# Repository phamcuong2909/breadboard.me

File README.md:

# breadboard.me
This contains all the sample codes and other resources for my blog at http://www.breadboard.me

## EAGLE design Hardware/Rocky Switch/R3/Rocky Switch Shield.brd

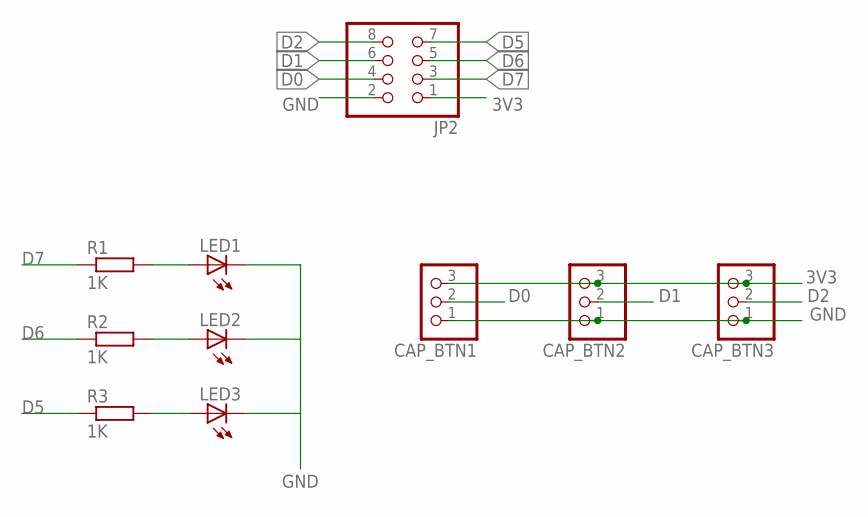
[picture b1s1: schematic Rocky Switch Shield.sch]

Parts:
CAP_BTN1, CAP_BTN2, CAP_BTN3: PINHD-1X3; 1X03
JP2: PINHD-2X4; 2X04
LED1, LED2, LED3: LED3MM
R1, R2, R3: 1K; R0805

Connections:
3V3: CAP_BTN1.3, CAP_BTN2.3, CAP_BTN3.3, JP2.1
D0: CAP_BTN1.2, JP2.4
D1: CAP_BTN2.2, JP2.6
D2: CAP_BTN3.2, JP2.8
D5: JP2.7, R3.1
D6: JP2.5, R2.1
D7: JP2.3, R1.1
GND: CAP_BTN1.1, CAP_BTN2.1, CAP_BTN3.1, JP2.2, LED1.K (C), LED2.K (C), LED3.K (C)
unnamed: LED2.A, R2.2
unnamed: LED3.A, R3.2
unnamed: LED1.A, R1.2

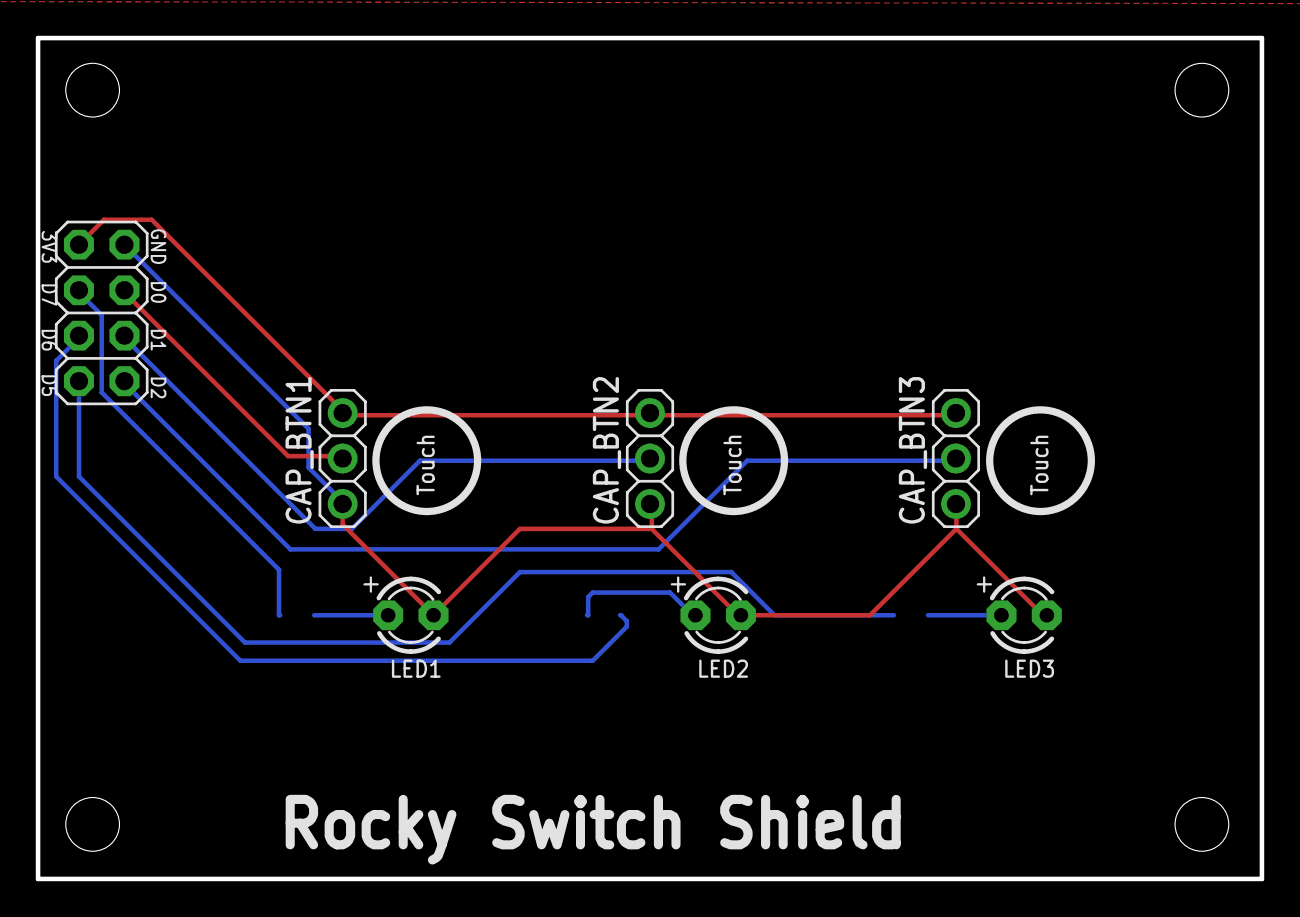
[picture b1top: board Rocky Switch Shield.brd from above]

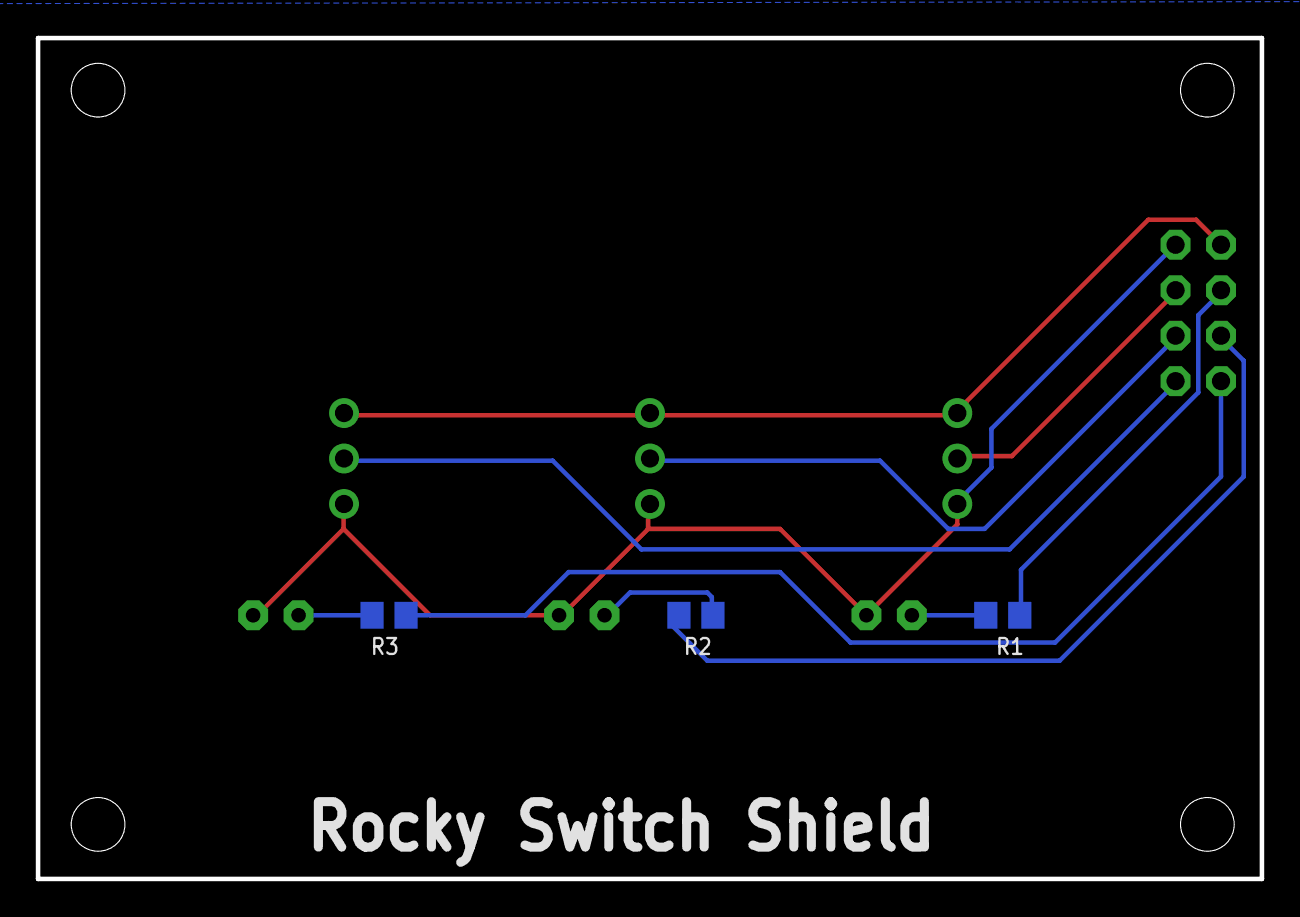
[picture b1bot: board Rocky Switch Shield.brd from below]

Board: 2 copper layers, 68.4 x 47.0 mm, 14 parts (3 on the bottom side), 11 nets.

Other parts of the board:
U$6, U$7, U$8, U$9: KFH-M3

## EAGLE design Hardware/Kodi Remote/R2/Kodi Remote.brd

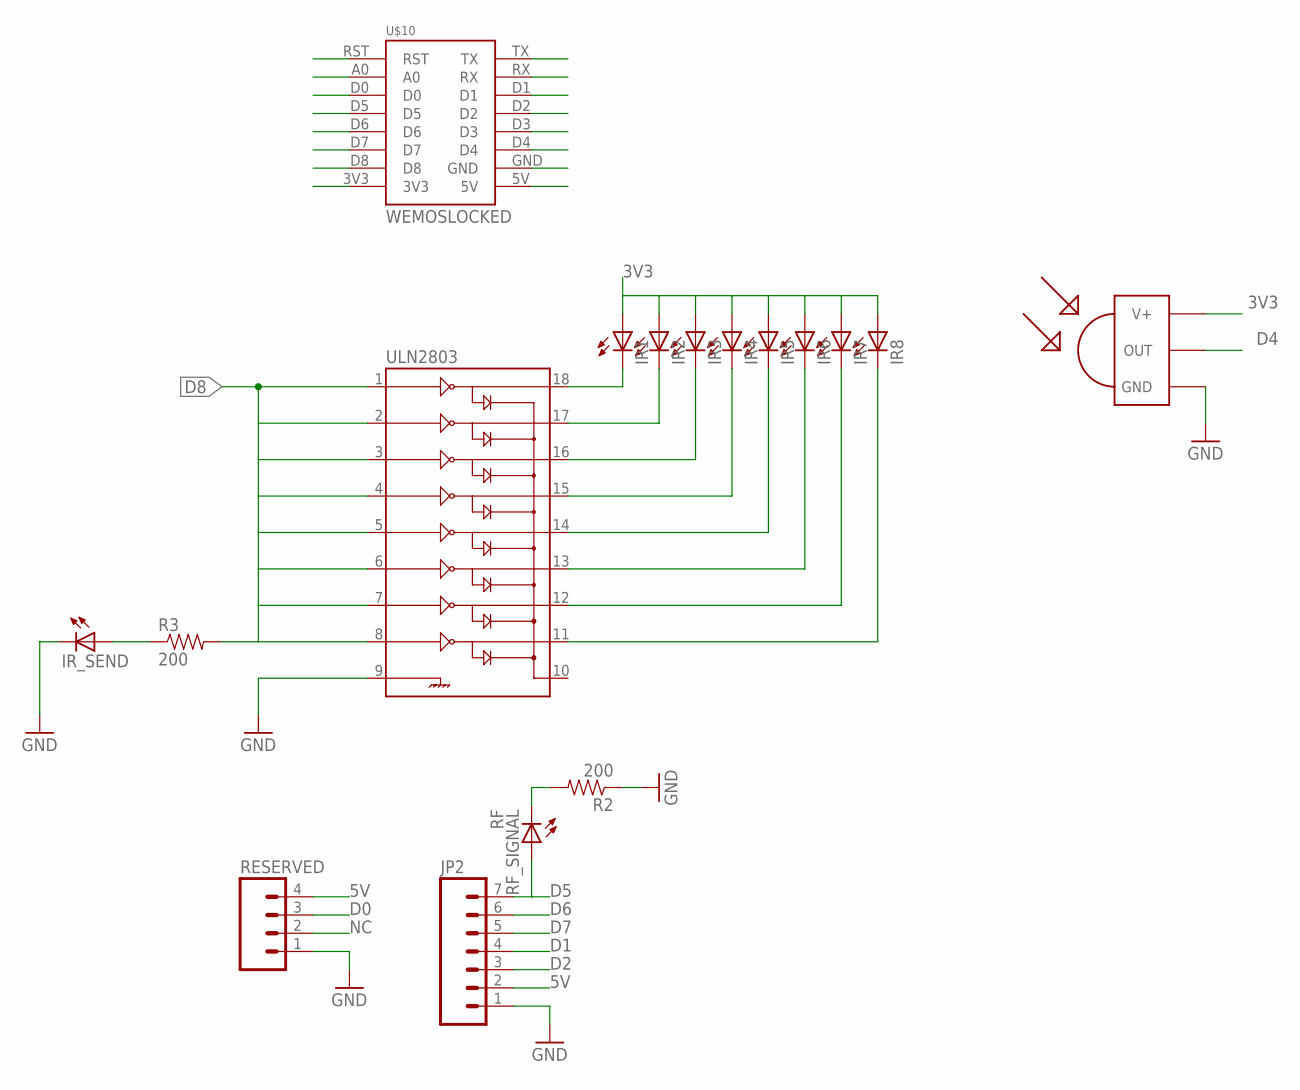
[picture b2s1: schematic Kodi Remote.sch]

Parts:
IR1, IR2, IR3, IR4, IR5, IR6, IR7, IR8: LED5MM
IR_SEND: LED3MM
JP2: M07; 1X07
R2, R3: 200; 0805
RESERVED: M04PTH; 1X04
RF_SIGNAL: RF; LED3MM
TSOP1838: TSOP1838; TSOP18XX
U$10: WEMOSLOCKED; WEMOS_LOCKED
ULN2803: ULN2803DIP; DIL18

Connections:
3V3: IR1.A, IR2.A, IR3.A, IR4.A, IR5.A, IR6.A, IR7.A, IR8.A, TSOP1838.VCC (V+), U$10.3V3
5V: JP2.2, RESERVED.4, U$10.5V
A0: U$10.A0
D0: RESERVED.3, U$10.D0
D1: JP2.4, U$10.D1
D2: JP2.3, U$10.D2
D3: U$10.D3
D4: TSOP1838.OUT, U$10.D4
D5: JP2.7, RF_SIGNAL.A, U$10.D5
D6: JP2.6, U$10.D6
D7: JP2.5, U$10.D7
D8: R3.2, U$10.D8, ULN2803.1, ULN2803.2, ULN2803.3, ULN2803.4, ULN2803.5, ULN2803.6, ULN2803.7, ULN2803.8
GND: IR_SEND.K (C), JP2.1, R2.1, RESERVED.1, TSOP1838.GND, U$10.GND, ULN2803.9
IR4: IR4.K (C), ULN2803.15
unnamed: R2.2, RF_SIGNAL.K (C)
unnamed: IR_SEND.A, R3.1
unnamed: IR1.K (C), ULN2803.18
unnamed: IR2.K (C), ULN2803.17
unnamed: IR3.K (C), ULN2803.16
unnamed: IR5.K (C), ULN2803.14
unnamed: IR6.K (C), ULN2803.13
unnamed: IR7.K (C), ULN2803.12
unnamed: IR8.K (C), ULN2803.11
NC: RESERVED.2
RST: U$10.RST
RX: U$10.RX
TX: U$10.TX

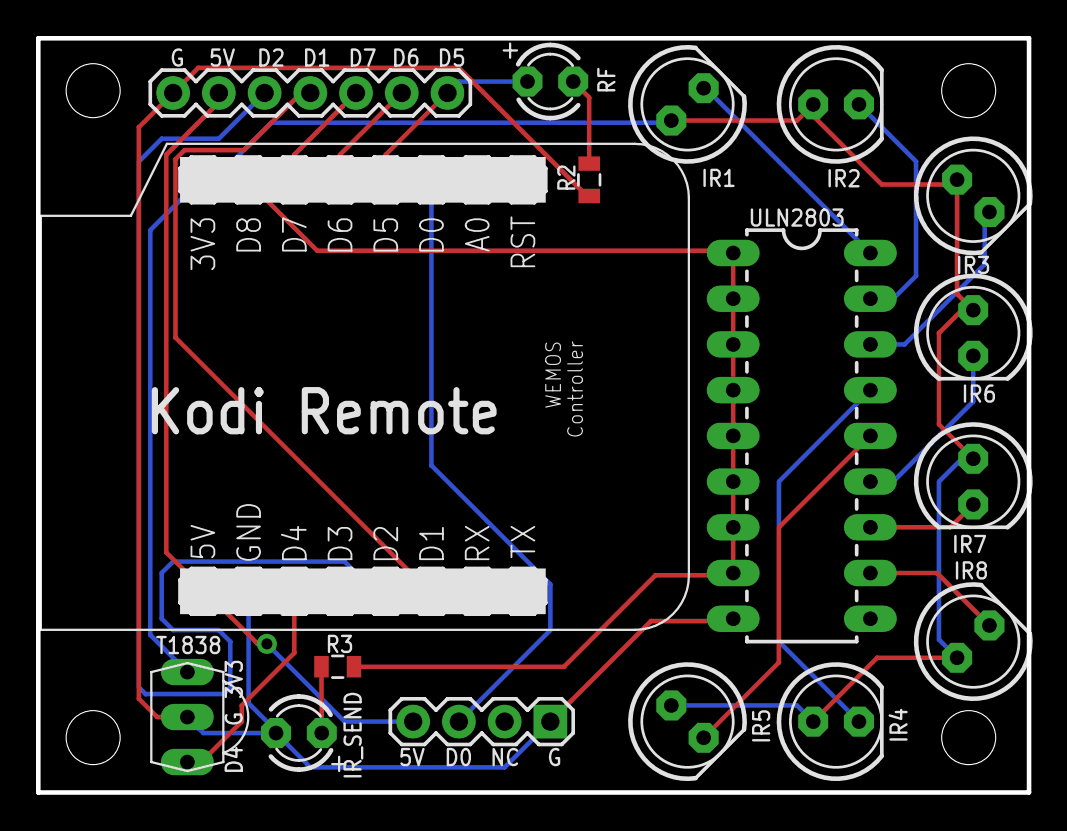
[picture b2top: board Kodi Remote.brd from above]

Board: 2 copper layers, 55.0 x 41.9 mm, 21 parts (0 on the bottom side), 21 nets.

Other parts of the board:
U$6, U$7, U$8, U$9: KFH-M3

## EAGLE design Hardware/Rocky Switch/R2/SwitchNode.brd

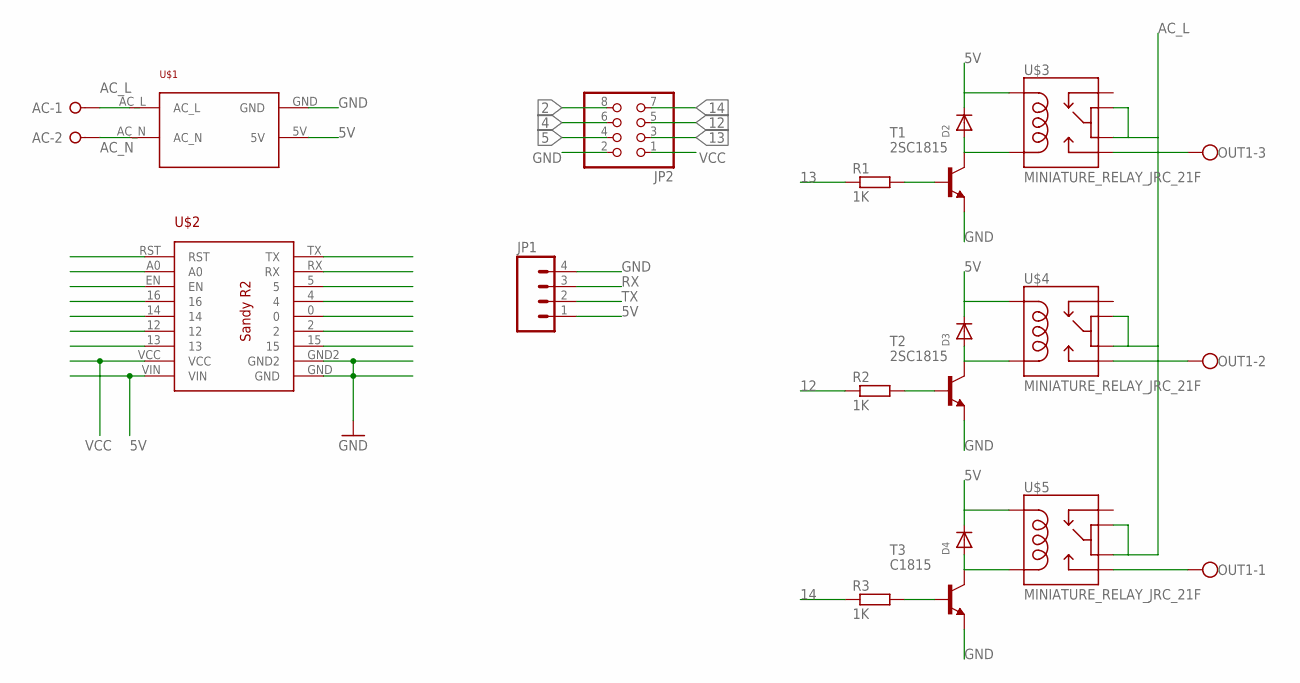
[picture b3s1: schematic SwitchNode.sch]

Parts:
AC: W237-02P; W237-132
D2, D3, D4: DIODESMA; SMADIODE
JP1: M04PTH; 1X04
JP2: PINHD-2X4; 2X04
OUT1: W237-103
R1, R2, R3: 1K; R0805
T1, T2: 2SC1815; TO92-ECB
T3: C1815; TO92-ECB
U$1: POWER_SUPPLY_220VAC_5V
U$2: MINI-ESP
U$3, U$4, U$5: MINIATURE_RELAY_JRC_21F

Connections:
0: U$2.0
2: JP2.8, U$2.2
4: JP2.6, U$2.4
5: JP2.4, U$2.5
5V: D2.C, D3.C, D4.C, JP1.1, U$1.5V, U$2.VIN, U$3.COIL1, U$4.COIL1, U$5.COIL1
12: JP2.5, R2.1, U$2.12
13: JP2.3, R1.1, U$2.13
14: JP2.7, R3.1, U$2.14
16: U$2.16
A0: U$2.A0
AC_L: AC.1, U$1.AC_L, U$3.COM1, U$3.COM2, U$4.COM1, U$4.COM2, U$5.COM1, U$5.COM2
AC_N: AC.2, U$1.AC_N
D8: U$2.15
EN: U$2.EN
GND: JP1.4, JP2.2, T1.E, T2.E, T3.E, U$1.GND, U$2.GND, U$2.GND2
unnamed: D2.A, T1.C, U$3.COIL2
unnamed: D3.A, T2.C, U$4.COIL2
unnamed: D4.A, T3.C, U$5.COIL2
unnamed: R3.2, T3.B
unnamed: R2.2, T2.B
unnamed: R1.2, T1.B
unnamed: OUT1.3, U$3.NO
unnamed: OUT1.1, U$5.NO
unnamed: OUT1.2, U$4.NO
RST: U$2.RST
RX: JP1.3, U$2.RX
TX: JP1.2, U$2.TX
VCC: JP2.1, U$2.VCC

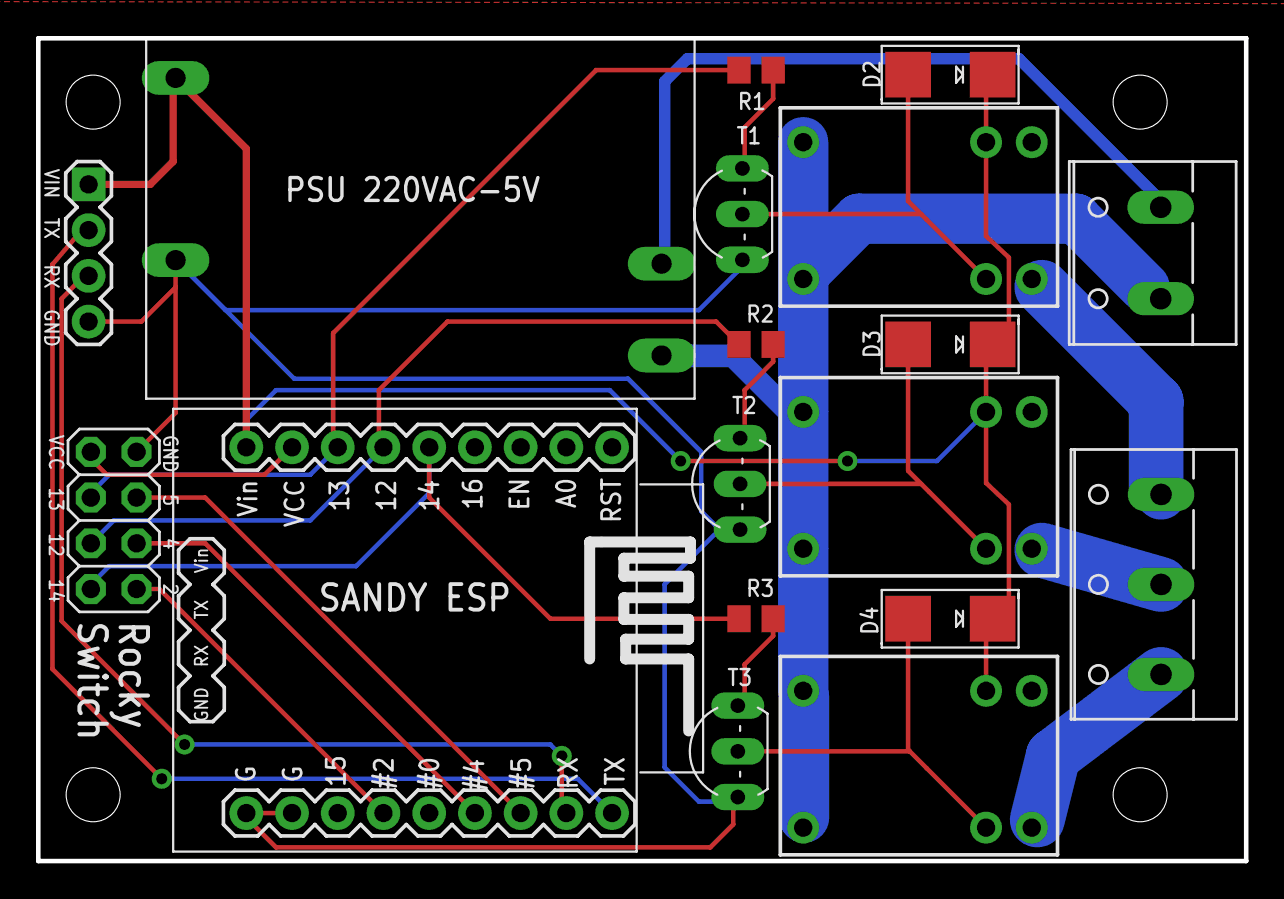
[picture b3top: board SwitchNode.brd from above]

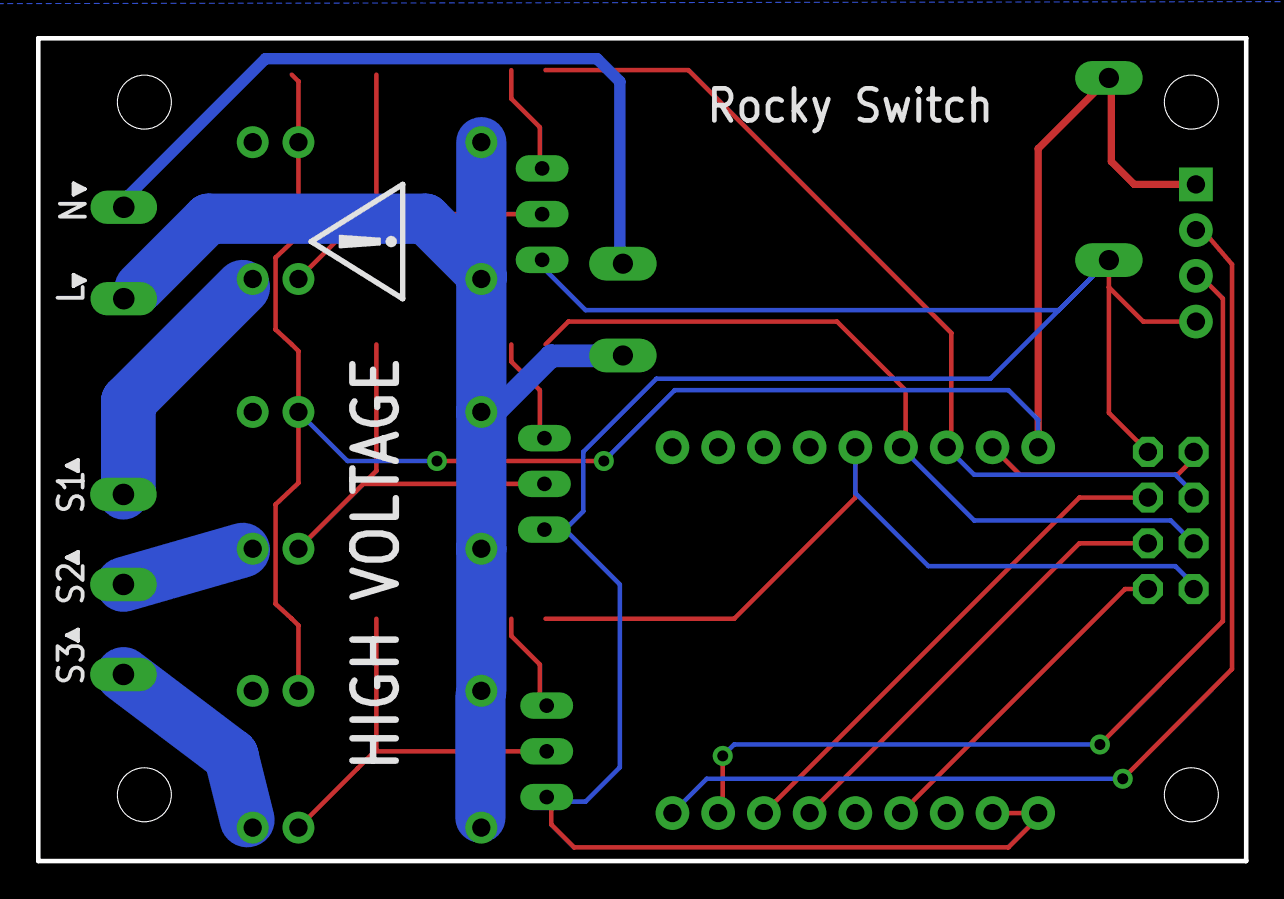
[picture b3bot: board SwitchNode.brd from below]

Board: 2 copper layers, 67.1 x 45.7 mm, 28 parts (6 on the bottom side), 22 nets.

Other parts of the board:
U$6, U$7, U$8, U$9: KFH-M3
U$11, U$12, U$13, U$14, U$15: ICON_PIN1_B
U$17: ICON_EXL-S

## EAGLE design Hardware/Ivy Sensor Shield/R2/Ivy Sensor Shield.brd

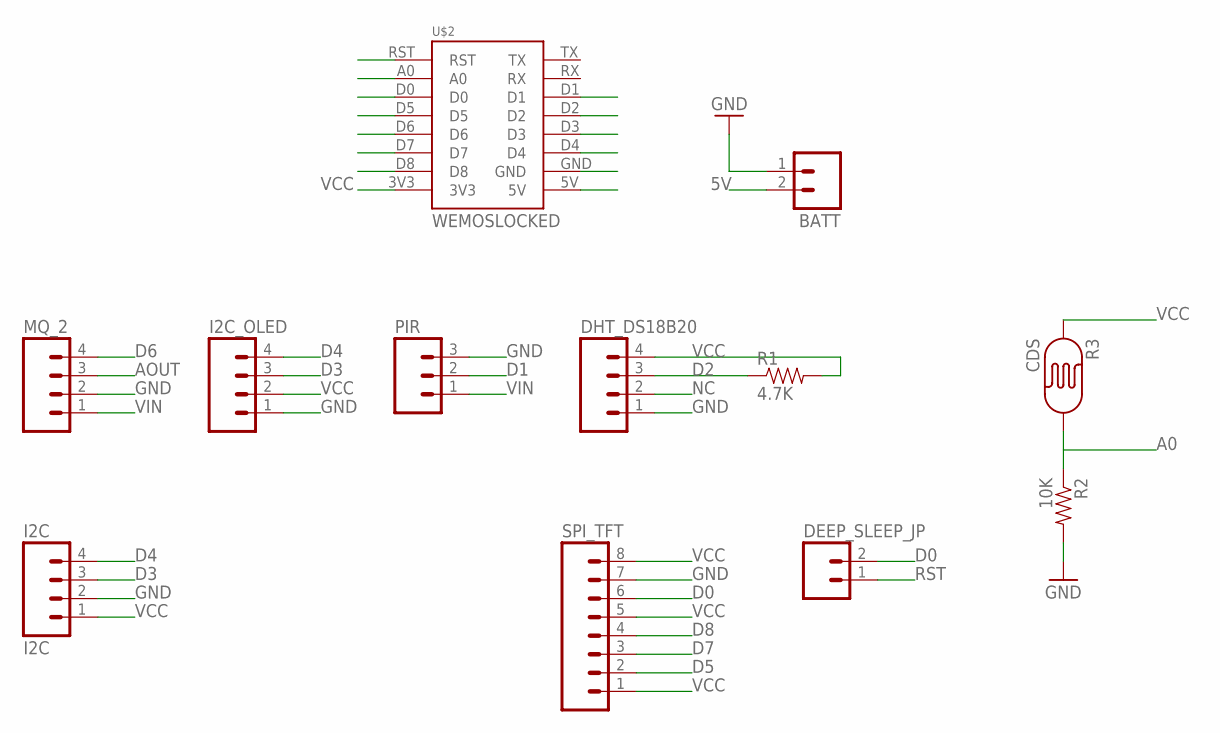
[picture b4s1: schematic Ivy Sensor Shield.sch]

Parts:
BATT: M02PTH; 1X02
DEEP_SLEEP_JP: M02PTH; 1X02
DHT_DS18B20: M04PTH; 1X04
I2C: I2C; 1X04
I2C_OLED: M04PTH; 1X04
MQ_2: M04PTH; 1X04
PIR: M03PTH; 1X03
R1: 4.7K; 0805
R2: 10K; 0805
R3: CDS; PHOTOCELL_THIN
SPI_TFT: M08; 1X08_ROUND
U$2: WEMOSLOCKED; WEMOS_LOCKED

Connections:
5V: BATT.2, U$2.5V
A0: R2.1, R3.2, U$2.A0
AOUT: MQ_2.3
D0: DEEP_SLEEP_JP.2, SPI_TFT.6, U$2.D0
D1: PIR.2, U$2.D1
D2: DHT_DS18B20.3, R1.1, U$2.D2
D3: I2C.3, I2C_OLED.3, U$2.D3
D4: I2C.4, I2C_OLED.4, U$2.D4
D5: SPI_TFT.2, U$2.D5
D6: MQ_2.4, U$2.D6
D7: SPI_TFT.3, U$2.D7
D8: SPI_TFT.4, U$2.D8
GND: BATT.1, DHT_DS18B20.1, I2C.2, I2C_OLED.1, MQ_2.2, PIR.3, R2.2, SPI_TFT.7, U$2.GND
NC: DHT_DS18B20.2
RST: DEEP_SLEEP_JP.1, U$2.RST
VCC: DHT_DS18B20.4, I2C.1, I2C_OLED.2, R1.2, R3.1, SPI_TFT.1, SPI_TFT.5, SPI_TFT.8, U$2.3V3
VIN: MQ_2.1, PIR.1

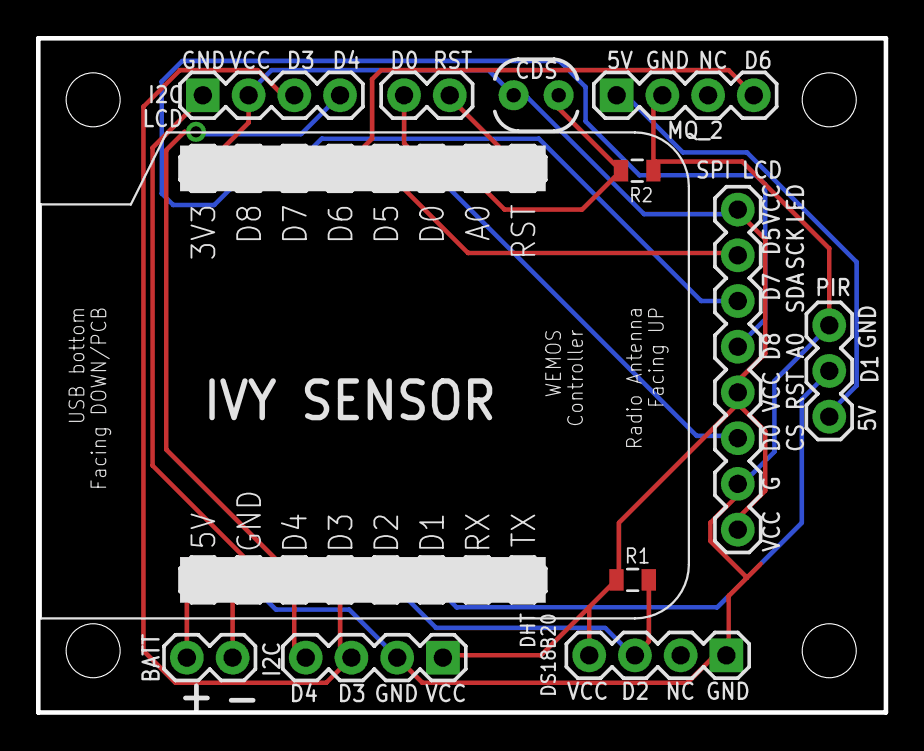
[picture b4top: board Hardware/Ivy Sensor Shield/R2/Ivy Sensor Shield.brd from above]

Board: 2 copper layers, 47.1 x 37.5 mm, 16 parts (0 on the bottom side), 15 nets.

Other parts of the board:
U$6, U$7, U$8, U$9: KFH-M3

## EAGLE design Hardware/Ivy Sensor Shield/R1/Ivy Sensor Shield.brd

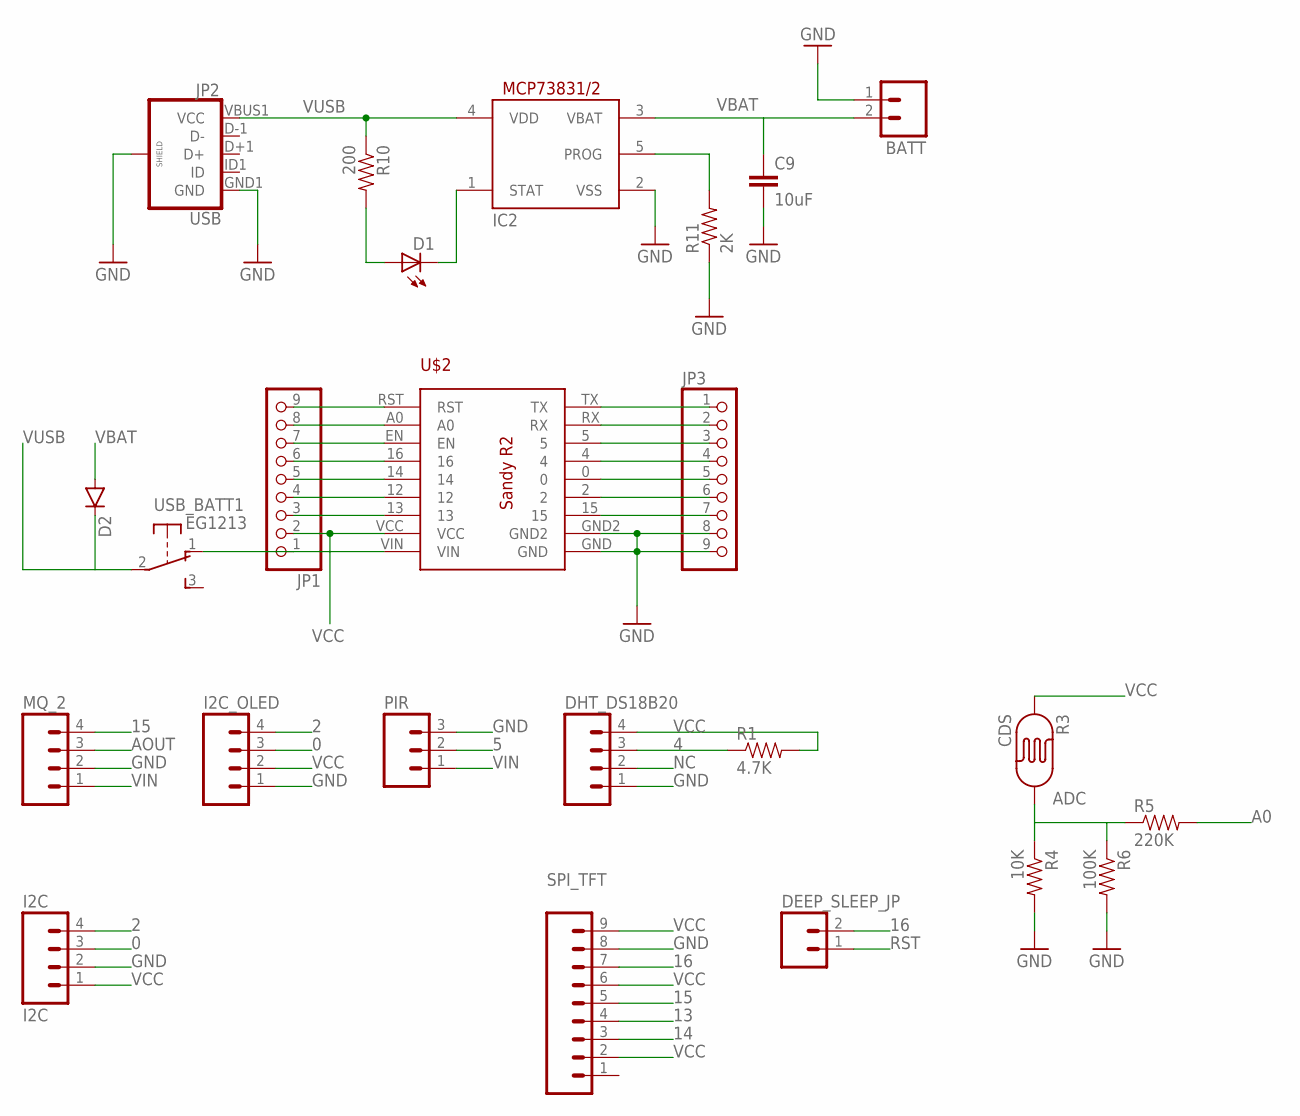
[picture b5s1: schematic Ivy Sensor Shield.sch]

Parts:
BATT: M02PTH; 1X02
C9: 10uF; 0805
D1: LEDCHIPLED_0805; CHIPLED_0805
D2: DIODESOD123; SOD-123
DEEP_SLEEP_JP: M02PTH; 1X02
DHT_DS18B20: M04PTH; 1X04
I2C: I2C; 1X04
I2C_OLED: M04PTH; 1X04
IC2: MCP73831/OT; SOT23-5L
JP1, JP3: PINHD-1X9; 1X09-BIG
JP2: USB; USB-B-MICRO-SMD_V03
MQ_2: M04PTH; 1X04
PIR: M03PTH; 1X03
R1: 4.7K; 0805
R3: CDS; PHOTOCELL_THIN
R4: 10K; 0805
R5: 220K; 0805
R6: 100K; 0805
R10: 200; 0805
R11: 2K; 0805
SPI_TFT: M09; 1X09
U$2: MINI-ESPMINI-ESP-LOCK; MINI-ESP-LOCK
USB_BATT: EG1213

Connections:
0: I2C.3, I2C_OLED.3, JP3.5, U$2.0
2: I2C.4, I2C_OLED.4, JP3.6, U$2.2
4: DHT_DS18B20.3, JP3.4, R1.1, U$2.4
5: JP3.3, PIR.2, U$2.5
12: JP1.4, U$2.12
13: JP1.3, SPI_TFT.4, U$2.13
14: JP1.5, SPI_TFT.3, U$2.14
15: JP3.7, MQ_2.4, SPI_TFT.5, U$2.15
16: DEEP_SLEEP_JP.2, JP1.6, SPI_TFT.7, U$2.16
A0: JP1.8, R5.2, U$2.A0
ADC: R3.2, R4.1, R5.1, R6.1
AOUT: MQ_2.3
EN: JP1.7, U$2.EN
GND: BATT.1, C9.2, DHT_DS18B20.1, I2C.2, I2C_OLED.1, IC2.2 (VSS), JP2.GND1 (GND), JP2.SHIELD1 (SHIELD), JP2.SHIELD2 (SHIELD), JP2.SHIELD3 (SHIELD), JP3.8, JP3.9, MQ_2.2, PIR.3, R4.2, R6.2, R11.1, SPI_TFT.8, U$2.GND, U$2.GND2
unnamed: D1.A, R10.2
NC: DHT_DS18B20.2
PROG: IC2.5 (PROG), R11.2
RST: DEEP_SLEEP_JP.1, JP1.9, U$2.RST
RX: JP3.2, U$2.RX
STAT: D1.C, IC2.1 (STAT)
TX: JP3.1, U$2.TX
VBAT: BATT.2, C9.1, D2.A, IC2.3 (VBAT)
VCC: DHT_DS18B20.4, I2C.1, I2C_OLED.2, JP1.2, R1.2, R3.1, SPI_TFT.2, SPI_TFT.6, SPI_TFT.9, U$2.VCC
VIN: JP1.1, MQ_2.1, PIR.1, U$2.VIN, USB_BATT.1 (O)
VUSB: D2.C, IC2.4 (VDD), JP2.VBUS1 (VCC), R10.1, USB_BATT.2

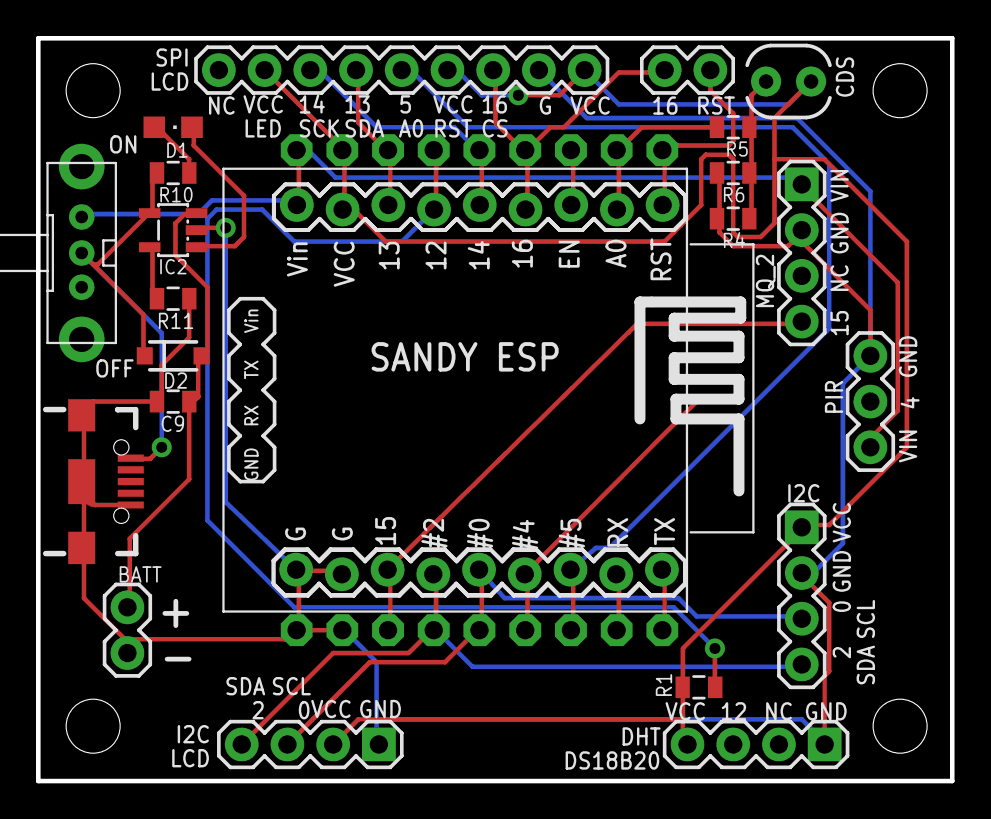
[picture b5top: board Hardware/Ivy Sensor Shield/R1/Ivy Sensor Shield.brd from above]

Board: 2 copper layers, 50.8 x 41.3 mm, 28 parts (0 on the bottom side), 23 nets.

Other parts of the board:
U$6, U$7, U$8, U$9: KFH-M3

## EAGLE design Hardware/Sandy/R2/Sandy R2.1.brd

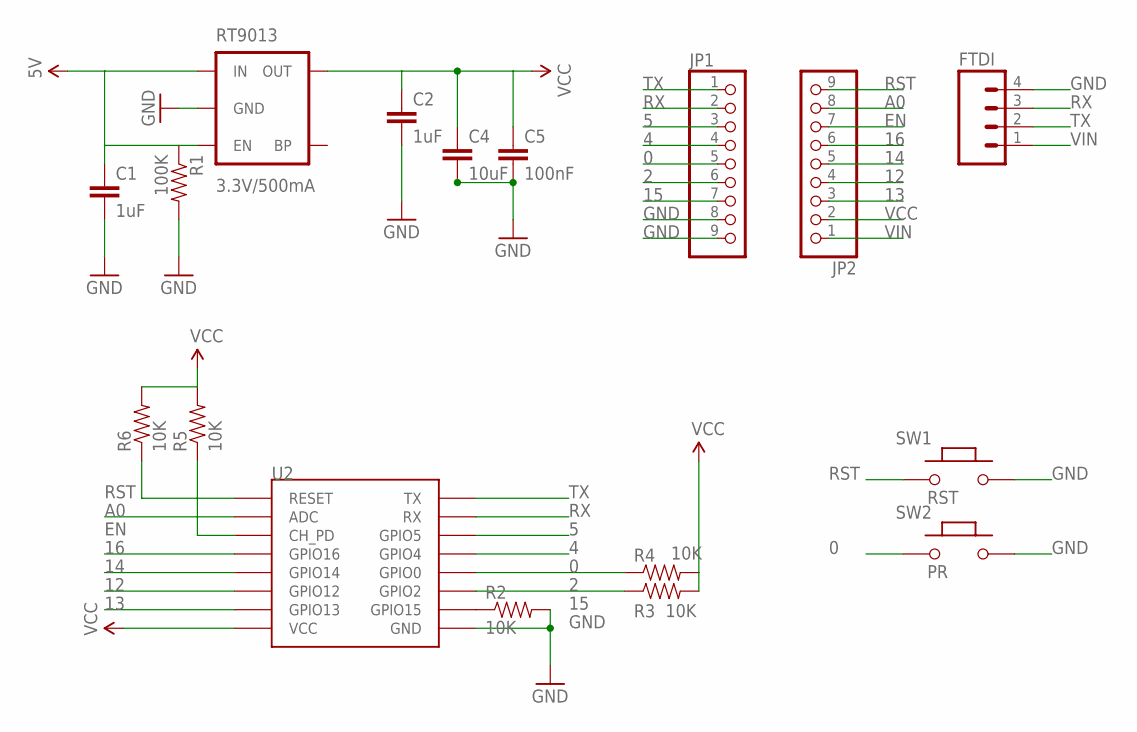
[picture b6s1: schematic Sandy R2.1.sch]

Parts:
C1, C2: 1uF; 0805
C4: 10uF; 0805
C5: 100nF; 0805
FTDI: M04PTH; 1X04
JP1, JP2: PINHD-1X9; 1X09-BIG
R1: 100K; 0805
R2, R3, R4, R5, R6: 10K; 0805
RT9013: 3.3V/500mA; SOT23-5
SW1: RST; 157SW
SW2: PR; 157SW
U2: ESP12THROUGHOLE; ESP12

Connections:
0: JP1.5, R4.1, SW2.1, U2.GPIO0
2: JP1.6, R3.1, U2.GPIO2
4: JP1.4, U2.GPIO4
5: JP1.3, U2.GPIO5
12: JP2.4, U2.GPIO12
13: JP2.3, U2.GPIO13
14: JP2.5, U2.GPIO14
15: JP1.7, R2.1, U2.GPIO15
16: JP2.6, U2.GPIO16
A0: JP2.8, U2.ADC
EN: JP2.7, R5.1, U2.CH_PD
GND: C1.2, C2.2, C4.2, C5.2, FTDI.4, JP1.8, JP1.9, R1.2, R2.2, RT9013.2 (GND), SW1.2, SW2.2, U2.GND
RST: JP2.9, R6.1, SW1.1, U2.RESET
RX: FTDI.3, JP1.2, U2.RX
TX: FTDI.2, JP1.1, U2.TX
VCC: C2.1, C4.1, C5.1, JP2.2, R3.2, R4.2, R5.2, R6.2, RT9013.5 (OUT), U2.VCC
VIN: C1.1, FTDI.1, JP2.1, R1.1, RT9013.1 (IN), RT9013.3 (EN)

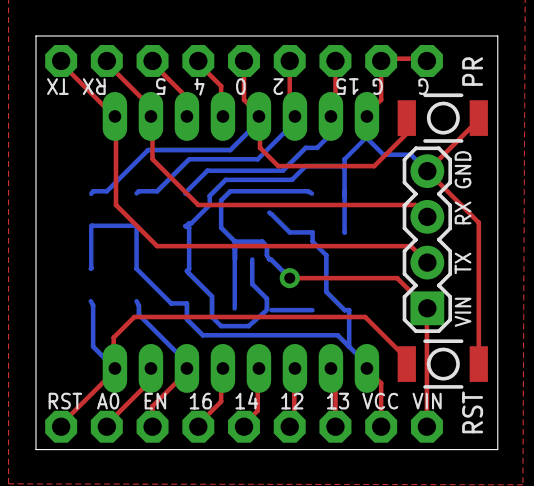
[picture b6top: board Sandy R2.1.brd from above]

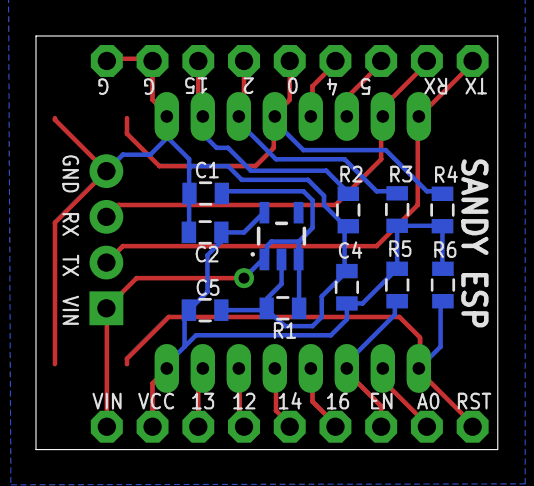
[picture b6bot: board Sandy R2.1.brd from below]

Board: 2 copper layers, 25.7 x 23.0 mm, 17 parts (11 on the bottom side), 17 nets.

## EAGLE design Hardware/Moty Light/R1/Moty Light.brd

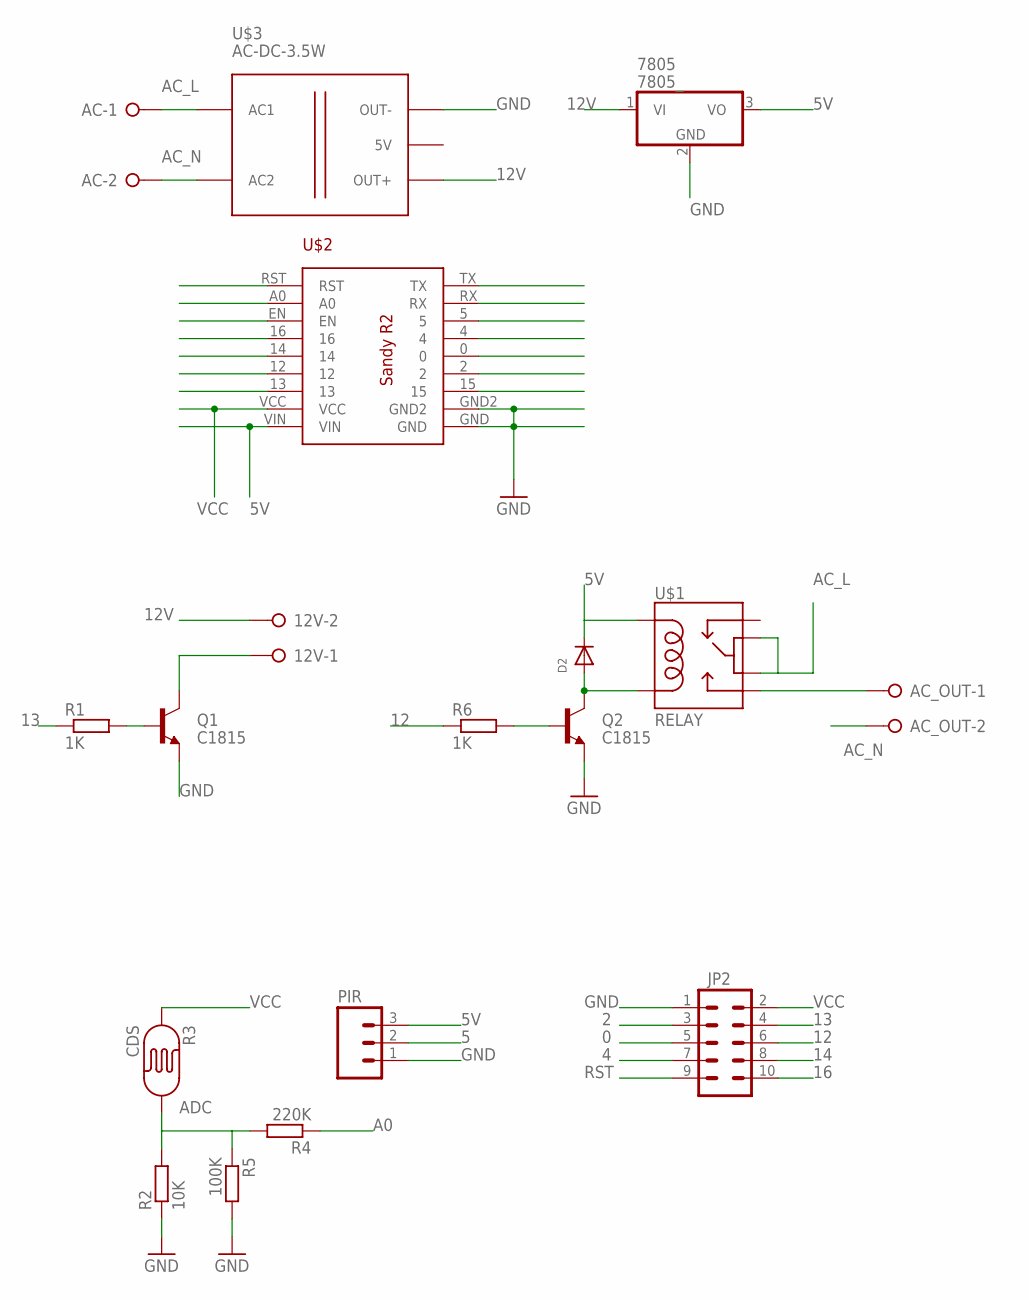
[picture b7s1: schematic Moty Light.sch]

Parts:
12V: W237-02P; W237-132
7805: 7805_; TO220V
AC: W237-02P; W237-132
AC_OUT: W237-02P; W237-132
D2: DIODESMA; SMADIODE
JP2: M05X2PTH; AVR_ICSP
PIR: M03PTH; 1X03
Q1, Q2: C1815; SOT23-3
R1, R6: 1K; R0805
R2: 10K; R0805
R3: CDS; PHOTOCELL_THIN
R4: 220K; R0805
R5: 100K; R0805
U$1: RELAY; MINIATURE_RELAY_JRC_21F
U$2: MINI-ESP
U$3: AC-DC-3.5W

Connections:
0: JP2.5, U$2.0
2: JP2.3, U$2.2
4: JP2.7, U$2.4
5: PIR.2, U$2.5
5V: 7805.3 (VO), D2.C, PIR.3, U$1.COIL1, U$2.VIN
12: JP2.6, R6.1, U$2.12
12V: 12V.2, 7805.1 (VI), U$3.J2.3 (OUT+)
13: JP2.4, R1.1, U$2.13
14: JP2.8, U$2.14
16: JP2.10, U$2.16
A0: R4.1, U$2.A0
AC_L: AC.1, U$1.COM1, U$1.COM2, U$3.J1.1 (AC1)
AC_N: AC.2, AC_OUT.2, U$3.J1.2 (AC2)
ADC: R2.2, R3.2, R4.2, R5.1
D8: U$2.15
EN: U$2.EN
GND: 7805.2 (GND), JP2.1, PIR.1, Q1.2 (E), Q2.2 (E), R2.1, R5.2, U$2.GND, U$2.GND2, U$3.J2.1 (OUT-)
unnamed: 12V.1, Q1.3 (C)
unnamed: D2.A, Q2.3 (C), U$1.COIL2
unnamed: Q2.1 (B), R6.2
unnamed: Q1.1 (B), R1.2
unnamed: AC_OUT.1, U$1.NO
RST: JP2.9, U$2.RST
RX: U$2.RX
TX: U$2.TX
VCC: JP2.2, R3.1, U$2.VCC

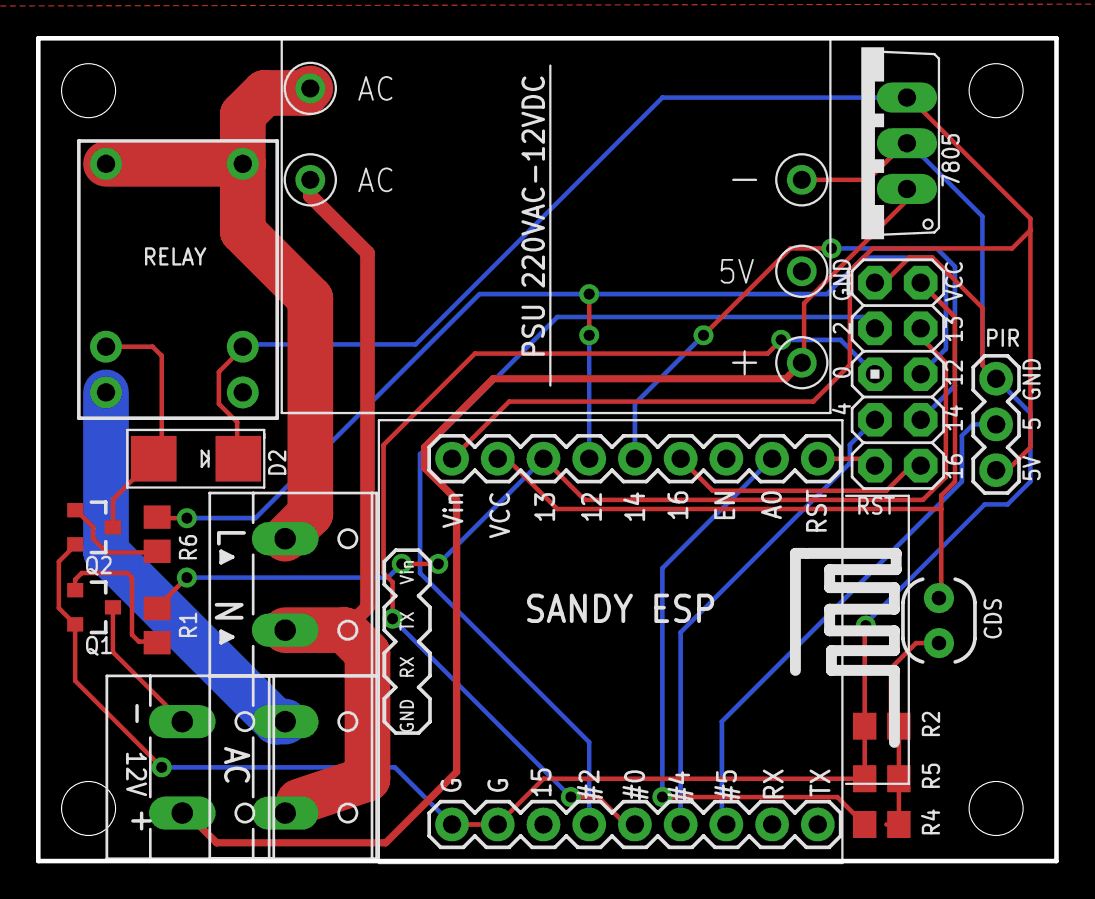
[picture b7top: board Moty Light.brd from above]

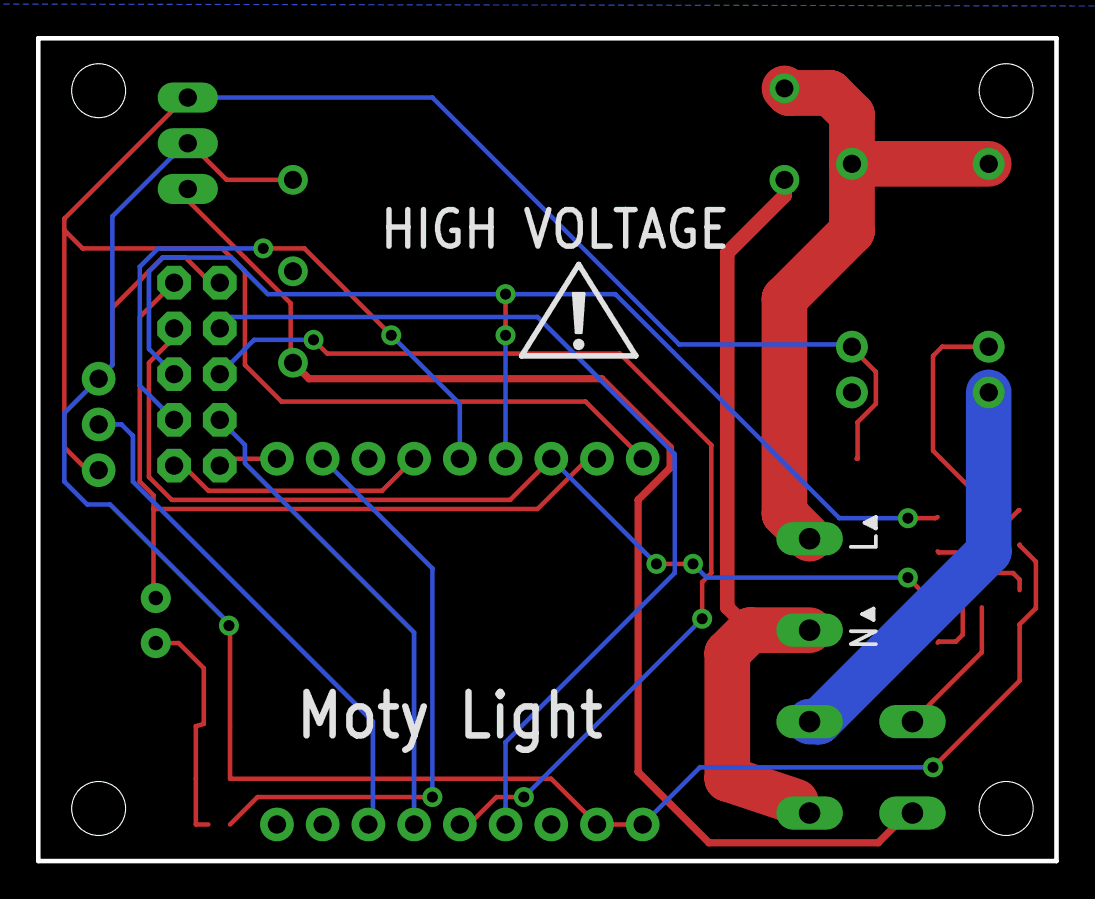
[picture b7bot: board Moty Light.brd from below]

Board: 2 copper layers, 56.6 x 45.7 mm, 27 parts (3 on the bottom side), 22 nets.

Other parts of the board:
U$4, U$5, U$11, U$12: ICON_PIN1_B
U$6, U$7, U$8, U$9: KFH-M3
U$17: ICON_EXL-S

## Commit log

2016-04-04 Add blink code file for esp8266
2016-04-04 Add sample code for blinking led through web
2016-04-06 Add sample code for ds18b20 temperature sensor
2016-04-06 Move all codes into Codes folder
2016-04-11 Add eagle file for Mini-esp and updated code for temp sensor
2016-04-13 Add board design files for SwitchNode and shield
2016-04-19 Add mini-esp r2 which is now called Sandy R2
2016-04-22 Update Mini-Esp and SwitchNode R2
2016-04-22 Rename Mini-Esp board to Sandy
2016-04-23 Correct PSU pinouts and update labels for SwitchNode R2
2016-04-23 Update Sandy R2: + Remove unused resistors and caps + Move 2 buttons to near side to better usability
2016-04-25 Add Moty Light board
2016-04-27 Update Sandy to move 2 switch buttons near rear side
2016-05-03 Update design for Moty Light
2016-05-03 Add design for Ivy Sensor shield
2016-05-04 Update Sandy R2 to be thinner
2016-05-04 Update Ivy Sensor to use locked pad version of Sandy Esp
2016-05-04 Add design for Kodi Remote
2016-05-10 Update Kodi Remote
2016-05-11 Update Kodi Remote to use locked version of Sandy Esp
2016-05-13 Update Kodi after first prototype
2016-05-16 Update Ivy Sensor to use Wemos D1 Mini
2016-05-17 Change Moty Light to use Wemos mini
2016-05-17 Update design for Kodi Remote to use Wemos D1 Mini
2016-05-17 Rename SwitchNode to Rocky Switch and change to use Wemos D1 Mini
2016-05-17 Minor change to Kodi Remote
2016-05-17 Correct wiring for Ivy Sensor Shield.brd
2016-05-18 Add design for Rocky Switch Shield.brd
2016-05-18 Remove obsolete switchnode shield
2016-06-10 Update code for introduction post
2016-06-10 Remove unused files
2016-06-10 Remove hardware design files and move them to separate projects
2016-06-10 Add sample config for openhab
2016-06-21 Add sample code for smart plug

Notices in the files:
parts and their libraries:
SparkFun: Licensing: CC v3.0 Share-Alike You are welcome to use this library for commercial purposes.
SparkFun-Connectors: Licensing: Creative Commons ShareAlike 4.0 International - https://creativecommons.org/licenses/by-sa/4.0
penn-engineering: Copyright (C) 2010, Bob Starr
